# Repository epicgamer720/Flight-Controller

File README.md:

# Rocket Flight Controller

A custom, open-source flight computer for model and high-power rockets, built around an STM32F722 with onboard IMU, barometer, GPS, pyro deployment, quad servo outputs, and microSD logging. Designed from scratch in KiCad.

## Why I built it

Wanted to get my feet wet with more mixed PCB design. I designed this as a base for firmware and testing I plan to designing another one after I build and test this one on actual rockets. I plan to use this for my rocketry team for active control and data logging 

## Use cases

- **Dual-deploy recovery**: pyro drogue at apogee, then a servo mechanically releases the main at a set altitude. (This rev routes one pyro channel; the servo is the second deploy.)
- **Active stabilization**: drive the four servo outputs for thrust-vector control or canard/fin steering during boost.
- **Flight data logging**: log IMU, barometer, and GPS to microSD for post-flight analysis (apogee, max velocity, flight path).
- **GPS tracking**: downrange tracking and finding the rocket after landing.
- **Telemetry**: LoRa (SX1262, 915 MHz) for live altitude/position downlink.
- **General avionics dev board**: the IMU + baro + GPS + servo + logging combo also works for drones, RC, robotics, or balloon payloads.

## Specifications

| Subsystem | Part / detail |
|---|---|
| MCU | STM32F722RET6, Cortex-M7, up to 216 MHz |
| IMU | ISM330DHCX, 6-axis accel (±16 g) + gyro, SPI (built rev; early docs said ICM-45686) |
| Barometer | BMP580, altitude / apogee detection (I²C) |
| Storage | microSD (SDMMC1, 4-bit), 200 Hz binary flight log |
| Recovery | 1 pyro channel (gate PB13, continuity sense PC1) + servo main-release, giving dual-deploy without a 2nd pyro (2 designed) |
| Control | 4× servo outputs (TIM2) for TVC / fin / canard; one doubles as the main-release |
| GPS | NMEA module on USART6, JST-GH + PRTR5V0U2X ESD protection |
| Telemetry | LoRa Wio-SX1262 (915 MHz, TCXO): live downlink + over-air TX-power control, verified on hardware |
| Power | 2S LiPo, BQ25883 charger, USB-C |
| Status | WS2812 RGB status LED |

## Bench status (July 2026)

All subsystems green on hardware: IMU, barometer, SD logging, LoRa radio
(TCXO confirmed, telemetry transmitting), charger, GPS UART. The firmware
builds with `arm-none-eabi-gcc` (GitHub CI), has been flashed to the board,
and passes its on-console **preflight** GO/NO-GO check, so it is **bench-verified,
not flight-tested**. The deploy-critical logic is exercised host-side by a SIL
harness (a faithful Python transcription of the state machine / Kalman / pyro
paths) plus 245 stdlib-`unittest` tests, and went through several adversarial
multi-agent review passes.

Flight hardening on top of the earlier IWDG watchdog + reset-cause logging,
Kalman altitude filter with outlier gating, and pad-drift baro tracking:

- **Hardened arm gate**: refuses to arm without pyro continuity, adequate
  battery, near-zero velocity, *and* a plausible skyward orientation
  (`ARM_UP_AXIS`).
- **Fault-independent backup deploy**: a backup timer fires the charge even
  through `ST_FAULT` with dead sensors, so a sensor loss isn't a lawn-dart.
- **Servo dual-deploy**: a main-release servo held SAFE through ascent,
  actuated at the main-deploy altitude (no 2nd pyro needed).
- **Flash config v2**: runtime-tunable apogee/backup timer + last-GPS-for-
  recovery, migrating cleanly from v1.
- **Telemetry v3**: sequence / packet-delivery ratio, last-event echo,
  main-alt read-back, STM32 die-temp, and over-air TX-power control.
- Gyro-cal stationarity check, IMU-freeze detection, self-healing ground
  FAULT, failed-deploy detection, deeper anti-replay nonce window, baro
  temperature compensation, a recovery LED strobe (WS2812), and a STOP-mode
  low-power `sleep`.

**Tune before flight**: the defaults are placeholders, not final: `ARM_UP_AXIS`
(confirm the skyward IMU axis), the apogee/backup timer per motor (`apogee`
console cmd), the servo endpoints, and the flight thresholds (`LAUNCH_G`,
`MAIN_ALT`, debounces). The baro-only Kalman also lags true apogee by ~70 m in
SIL at `KAL_Q_ACCEL=4`, a candidate to raise once real flight data exists.
Also remaining: ground-station pin map + build, and a healthier USB cable.

## BOM

| Name | Purpose | Qty | Unit Cost (USD) | Line Cost (USD) | Link | Distributor | Notes |
|---|---|---|---|---|---|---|---|
| 1uF | Decoupling cap (0603, X7R, 25V) | 4 | $0.02 | $0.08 | Link | Digikey | |
| 10uF | Bulk decoupling (0805, X5R, 16V) | 7 | $0.10 | $0.40 | Link | Digikey | |
| 47nF | Filter cap, possibly BQ25883 ILIM or feedback (0603) | 1 | $0.02 | $0.02 | Link | Digikey | |
| 44uF | Unusual value, check schematic | 1 | $0.50 | $0.50 | Link | Digikey |  |
| 10uF | Bulk decoupling (0805, X5R) | 2 | $0.10 | $0.20 | Link | Digikey | |
| 22uF | Switching regulator output cap (0805, X5R, 16V) | 3 | $0.20 | $0.60 | Link | Digikey | |
| 100nF | Generic decoupling, 0402 or 0603 X7R | 12 | $0.01 | $0.12 | Link | Digikey | |
| 2.2uF | STM32 VCAP_1 (PA0) capacitor, 2.2µF X7R 0603 | 1 | $0.05 | $0.05 | Link | Digikey | Critical for MCU core regulator stability |
| 22uF | Regulator input/output cap | 2 | $0.20 | $0.40 | Link | Digikey | |
| 2.2uF | Second VCAP or filter | 1 | $0.05 | $0.05 | Link | Digikey | |
| 20pF | HSE crystal load capacitor (matches X322525MOB4SI) | 2 | $0.05 | $0.10 | Link | Digikey | Value depends on crystal CL spec, verify |
| 6.8pF | LSE 32.768kHz crystal load capacitor | 2 | $0.05 | $0.10 | Link | Digikey | Adjust to match crystal CL = ~7pF |
| 100nF | Generic decoupling, 0402 or 0603 | 5 | $0.01 | $0.05 | Link | Digikey | |
| TF-01A | MicroSD card socket (push-pull or hinged) | 1 | $1.50 | $1.50 | Link | LCSC | LCSC-style part; Hirose DM3AT-SF-PEJM5 is a Digikey alternative |
| LED | Generic indicator LED 0603 (e.g., power indicator) | 1 | $0.10 | $0.10 | Link | Digikey | |
| WS2812B-2020 | Addressable RGB status LED, single-wire (KMK-style) | 1 | $0.30 | $0.30 | Link | LCSC | Cheaper on LCSC than Digikey |
| PRTR5V0U2X | Dual-line TVS ESD protection for GPS UART | 1 | $0.35 | $0.35 | Link | Digikey | Nexperia, SOT-143B |
| Screw_Terminal_01x02 | 2-pin screw terminal for pyro outputs and battery | 3 | $1.20 | $3.60 | Link | Digikey | |
| BM05B-GHS-TBT_LF__SN__N_ | JST-GH 5-pin top-entry connector (GPS, Pixhawk standard) | 1 | $0.55 | $0.55 | Link | Digikey | JST part #BM05B-GHS-TBT(LF)(SN)(N) |
| FCM1608KF-601T03 | Ferrite bead 600Ω @ 100MHz, 0603, analog supply filter | 1 | $0.10 | $0.10 | Link | Digikey | Taiyo Yuden |
| DFE252012F-1R0M=P2 | Power inductor 1.0µH, 2520 case, buck output (LMR51430?) | 1 | $0.40 | $0.40 | Link | Digikey | Toko/Murata, ~3.6A saturation |
| XFL4020-152MEC | Power inductor 1.5µH, 4×4mm, switcher output | 1 | $1.50 | $1.50 | Link | Digikey | Coilcraft, very low DCR |
| YHNR3015-5R6M | Power inductor 5.6µH, likely buck-boost (TPS63070) | 1 | $0.30 | $0.30 | Link | LCSC | Sunlord, LCSC-stocked |
| AO3400A | N-channel logic-level MOSFET, SOT-23, pyro low-side switch | 2 | $0.15 | $0.30 | Link | Digikey | |
| 5.1K Ohm | Pullup/divider for USB-C CC1/CC2 (5.1k for device-mode detect) | 2 | $0.01 | $0.02 | Link | Digikey | Required for USB-C device mode |
| .383k Ohm | Precision resistor, likely BQ25883 ISET or regulator FB | 1 | $0.10 | $0.10 | Link | Digikey | |
| 5.23K Ohm | Feedback divider for switching regulator | 1 | $0.05 | $0.05 | Link | Digikey | 1% precision |
| 30.1K Ohm | Feedback divider (top resistor) for switching regulator | 1 | $0.05 | $0.05 | Link | Digikey | 1% precision |
| 10K Ohm | Generic pullups/pulldowns, gate pulldowns on MOSFETs (0603) | 19 | $0.01 | $0.19 | Link | Digikey | Cheap in bulk |
| 100K Ohm | Continuity divider top (pyro sense) | 1 | $0.01 | $0.01 | Link | Digikey | |
| 22.1K Ohm | Precision feedback or current-set resistor | 1 | $0.05 | $0.05 | Link | Digikey | 1% precision |
| 100K Ohm | More continuity dividers | 2 | $0.01 | $0.02 | Link | Digikey | |
| 100 Ohm | Gate series resistors on pyro MOSFETs | 3 | $0.01 | $0.03 | Link | Digikey | |
| Conn_01x03 | 3-pin header, likely servo/PWM outputs or programming | 4 | $0.30 | $1.20 | Link | Digikey | (2.54mm standard) |
| TS-1088-AR02016 | Tactile switch for boot/reset buttons | 2 | $0.20 | $0.40 | Link | Digikey | Cheap SMD tactile, also on LCSC |
| STM32F722RETx | Main MCU, ARM Cortex-M7, 216MHz, 512KB flash | 1 | $10.50 | $10.50 | Link | Digikey/Mouser | Check stock: F7 series can be supply-constrained |
| BQ25883RGER | Single-cell Li-ion charger w/ I2C, up to 2A | 1 | $3.80 | $3.80 | Link | Digikey | TI, QFN-24 |
| ICM-45686 | 6-axis IMU (accel + gyro), low-noise, SPI | 1 | $12.00 | $12.00 | Link | Digikey | TDK InvenSense, LGA-14. Newer than ICM-42688-P |
| BMP580 | Barometric pressure / altitude sensor (high resolution) | 1 | $4.20 | $4.20 | Link | Digikey | Bosch Sensortec, replaces BMP388 |
| TPS63070RNMR | Buck-boost regulator, 2A, 2-16V in | 1 | $3.60 | $3.60 | Link | Digikey | TI, VQFN-15 |
| LMR51430 | Buck regulator, 3A, simple step-down | 1 | $1.40 | $1.40 | Link | Digikey | TI, SOT-23-6 family |
| TYPE-C 16PIN 2MD(073) | USB-C connector, 16-pin (USB 2.0 only) | 1 | $0.50 | $0.50 | Link | LCSC | LCSC-style part number. Alt: GCT USB4105-GF-A (Digikey) |
| X322525MOB4SI | HSE crystal 25MHz, SMD 3225 | 1 | $0.60 | $0.60 | Link | LCSC | Yangxing. Alt: Abracon ABM8G-25.000MHZ |
| Q13FC1350000400 | LSE crystal 32.768kHz (RTC) | 1 | $0.40 | $0.40 | Link | Digikey | Epson FC-135 |

## Firmware & software

The flight firmware and ground tools live in this repo:

| Where | What |
|---|---|
| [`flight-controller/`](flight-controller/) | STM32F722 flight firmware: sensors, Kalman altitude filter, flight state machine, hardened arm gate + interlocked pyro control, fault-independent backup deploy, servo main-release, flash config v2, SD logging, LoRa telemetry v3 (die-temp + TX-power control), IWDG watchdog, USB console (`preflight`, `apogee`, `sleep`, …) |
| [`ground-station/`](ground-station/) | RP2040 + SX1262 LoRa ground station (RadioLib sketch; pin map pending) |
| [`shared/`](shared/) | `protocol.h`, the single source of truth for the radio link + packet formats |
| [`tools/`](tools/) | **Flight Deck** ops dashboard (recovery bearing/distance, baro-vs-GPS apogee check, telemetry-loss alarm, satellite GPS ground-track, SD `.bin` replay), one-page flight report, DFU flash helper (`flash.py`), serial monitor, log/telemetry decoders (`decode_log.py --summary`) |
| [`tests/`](tests/) | 245 host-side unit tests + a SIL flight harness (`py -m unittest discover -s tests`) |
| [`docs/FIRMWARE.md`](docs/FIRMWARE.md) | build / flash / console / bench guide |
| [`docs/PINMAP.md`](docs/PINMAP.md) | authoritative pin map extracted from the KiCad netlist |

## This project uses:

- [KiCad](https://www.kicad.org/)
- [STM32CubeMX](https://www.st.com/en/development-tools/stm32cubemx.html)
- [easyeda2kicad.py](https://github.com/uPesy/easyeda2kicad.py)
- [Hack Club Blueprint](https://blueprint.hackclub.com/)

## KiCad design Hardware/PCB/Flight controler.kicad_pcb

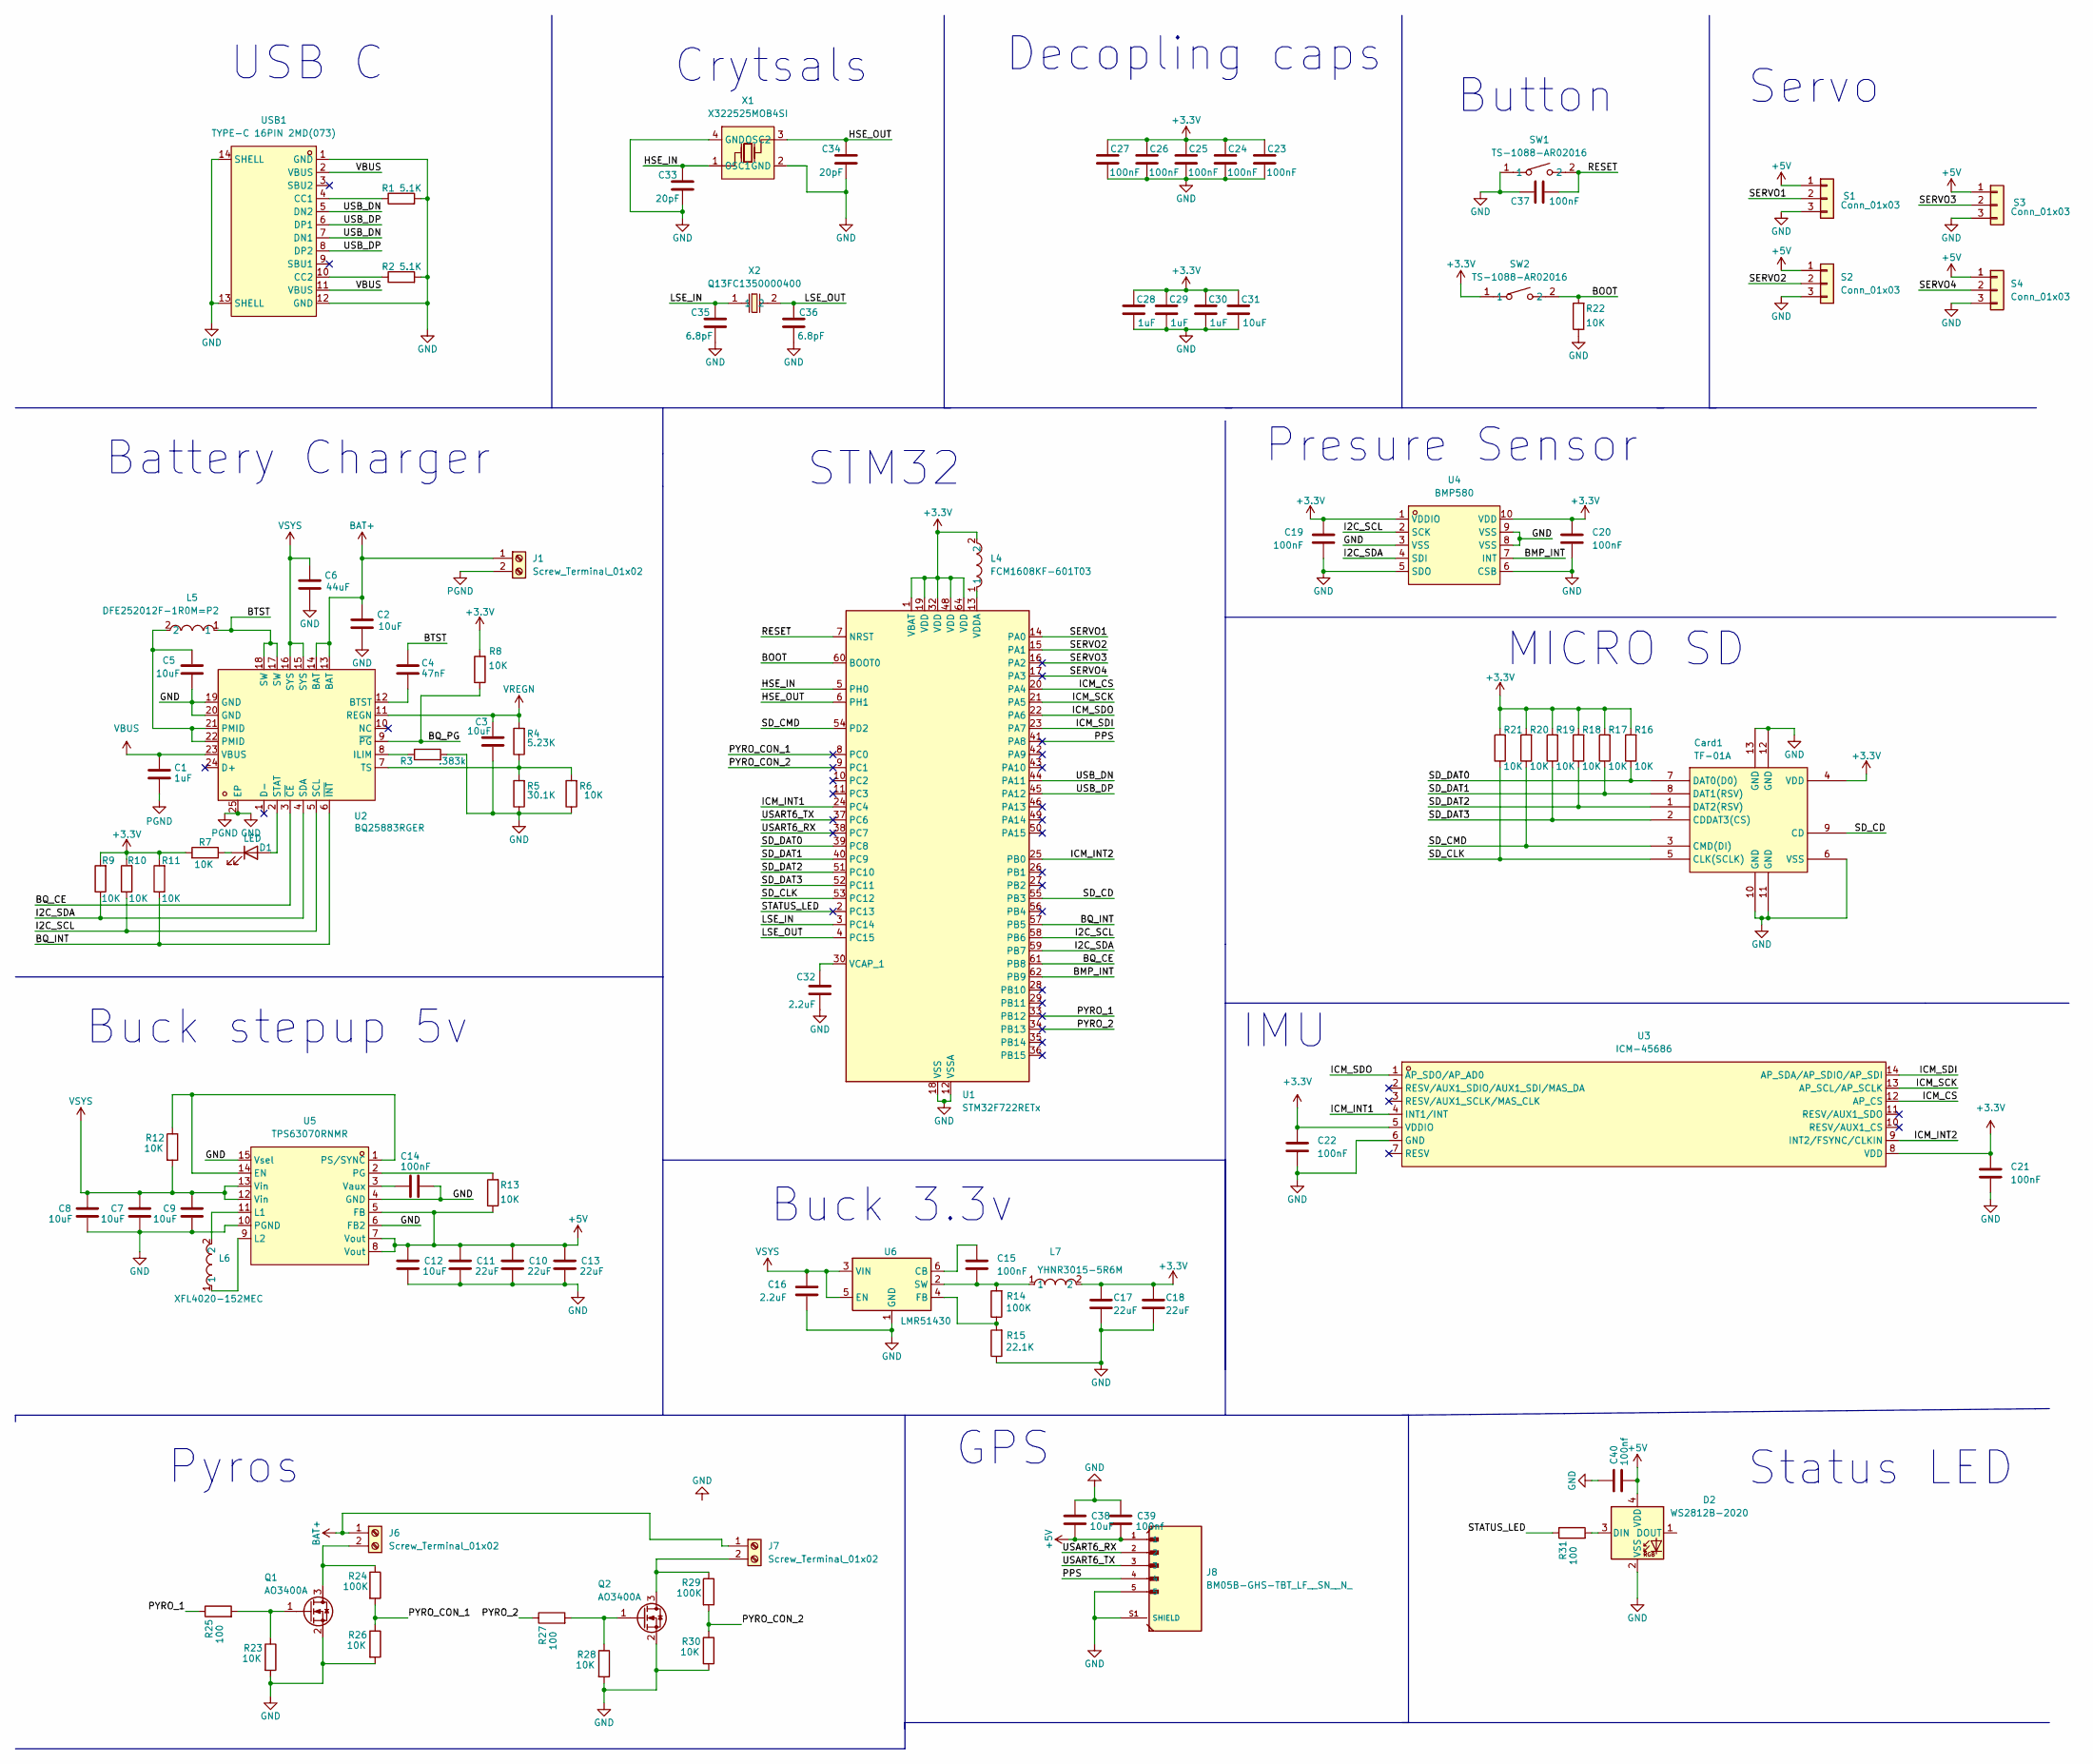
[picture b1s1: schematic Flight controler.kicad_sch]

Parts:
C1, C28, C29, C30: 1uF; C_0402_1005Metric
C2, C9, C12, C38: 10uF; C_0603_1608Metric
C3, C5, C31: 10uF; C_0402_1005Metric
C4: 47nF; C_0201_0603Metric
C6: 44uF; C_0603_1608Metric
C7, C8: 10uF; C_0805_2012Metric
C10, C11, C13: 22uF; C_0805_2012Metric
C14, C15, C19, C20, C21, C22, C23, C24, C25, C26, C27, C37: 100nF; C_0201_0603Metric
C16: 2.2uF; C_0603_1608Metric
C17, C18: 22uF; C_0402_1005Metric
C32: 2.2uF; C_0201_0603Metric
C33, C34: 20pF; C_0201_0603Metric
C35, C36: 6.8pF; C_0201_0603Metric
C39, C40: 100nf; C_0603_1608Metric
Card1: TF-01A; TF-SMD_TF-01A; LCSC Part C91145
D1: LED; LED_0402_1005Metric
D2: WS2812B-2020; LED_WS2812B-2020_PLCC4_2.0x2.0mm
J1, J6, J7: Screw_Terminal_01x02; TerminalBlock_Xinya_XY308-2.54-2P_1x02_P2.54mm_Horizontal
J8: BM05B-GHS-TBT_LF__SN__N_; JST_BM05B-GHS-TBT_LF__SN__N_
L4: FCM1608KF-601T03; L0603; LCSC Part C141723
L5: DFE252012F-1R0M=P2; L2520; LCSC Part C435392
L6: XFL4020-152MEC; IND-SMD_L4.0-W4.0-A; LCSC Part C3033018
L7: YHNR3015-5R6M; IND-SMD_L3.0-W3.0; LCSC Part C18236327
Q1, Q2: AO3400A; SOT-23
R1, R2: 5.1K; R_0201_0603Metric
R3: .383k; R_0201_0603Metric
R4: 5.23K; R_0201_0603Metric
R5: 30.1K; R_0201_0603Metric
R6, R7, R8, R9, R10, R11, R12, R13, R16, R17, R18, R19, R20, R21, R22, R23, R26, R28, R30: 10K; R_0201_0603Metric
R14: 100K; R_0402_1005Metric
R15: 22.1K; R_0402_1005Metric
R24, R29: 100K; R_0201_0603Metric
R25, R27, R31: 100; R_0201_0603Metric
S1, S2, S3, S4: Conn_01x03; PinHeader_1x03_P2.54mm_Vertical
SW1, SW2: TS-1088-AR02016; SW-SMD_L3.9-W3.0-P4.45; LCSC Part C720477
U1: STM32F722RETx; LQFP-64_10x10mm_P0.5mm
U2: BQ25883RGER; VFQFPN-24_L4.0-W4.0-P0.50-BL-EP2.8; LCSC Part C544362
U3: ICM-45686; LGA-14_L3.0-W2.5-P0.50-TL; LCSC Part C22459454
U4: BMP580; LGA-10_L2.0-W2.0-P0.50-TL_BMP580; LCSC Part C22391138
U5: TPS63070RNMR; VQFN-HR-15_L3.0-W2.5-P0.50-BL_TPS63070RNMR; LCSC Part C109322
U6: LMR51430; SOT-23-6
USB1: TYPE-C 16PIN 2MD(073); USB-C-SMD_TYPE-C-6PIN-2MD-073; LCSC Part C2765186
X1: X322525MOB4SI; CRYSTAL-SMD_4P-L3.2-W2.5-BL; LCSC Part C9006
X2: Q13FC1350000400; FC-135R_L3.2-W1.5; LCSC Part C32346

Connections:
+3.3V: C17.1, C18.1, C19.1, C20.1, C21.1, C22.1, C23.1, C24.1, C25.1, C26.1, C27.1, C28.1, C29.1, C30.1, C31.1, Card1.4 (VDD), L4.2, L7.2, R7.2, R8.2, R9.2, R10.2, R11.2, R16.2, R17.2, R18.2, R19.2, R20.2, R21.2, SW2.1, U1.1 (VBAT), U1.19 (VDD), U1.32 (VDD), U1.48 (VDD), U1.64 (VDD), U3.5 (VDDIO), U3.8 (VDD), U4.1 (VDDIO), U4.10 (VDD); also elsewhere on the board
+5V: C10.1, C11.1, C12.1, C13.1, C38.2, C39.2, C40.2, D2.4 (VDD), J8.1, R13.1, S1.1, S2.1, S3.1, S4.1, U5.5 (FB), U5.7 (Vout), U5.8 (Vout); also elsewhere on the board
/BMP_INT: U1.62 (PB9), U4.7 (INT)
/BOOT: R22.2, SW2.2, U1.60 (BOOT0); also elsewhere on the board
/BQ_CE: U1.61 (PB8), U2.3 (~CE)
/BQ_INT: R11.1, U1.57 (PB5), U2.6 (~INT)
/BQ_PG: R8.1, U2.9 (~PG)
/BTST: C4.1, L5.1, U2.17 (SW), U2.18 (SW)
/HSE_IN: C33.1, U1.5 (PH0), X1.1 (OSC1)
/HSE_OUT: C34.1, U1.6 (PH1), X1.3 (OSC2)
/I2C_SCL: R10.1, U1.58 (PB6), U2.5 (SCL), U4.2 (SCK)
/I2C_SDA: R9.1, U1.59 (PB7), U2.4 (SDA), U4.4 (SDI)
/ICM_CS: U1.20 (PA4), U3.12 (AP_CS)
/ICM_INT1: U1.24 (PC4), U3.4 (INT1/INT)
/ICM_INT2: U1.25 (PB0), U3.9 (INT2/FSYNC/CLKIN)
/ICM_SCK: U1.21 (PA5), U3.13 (AP_SCL/AP_SCLK)
/ICM_SDI: U1.23 (PA7), U3.14 (AP_SDA/AP_SDIO/AP_SDI)
/ICM_SDO: U1.22 (PA6), U3.1 (AP_SDO/AP_AD0)
/LSE_IN: C35.1, U1.3 (PC14), X2.1
/LSE_OUT: C36.1, U1.4 (PC15), X2.2
/PPS: J8.4, U1.41 (PA8)
/PYRO_1: R25.1, U1.33 (PB12)
/PYRO_2: R27.1, U1.34 (PB13)
/PYRO_CON_1: R24.2, R26.1, U1.8 (PC0)
/PYRO_CON_2: R29.2, R30.1, U1.9 (PC1)
/RESET: C37.2, SW1.2, U1.7 (NRST); also elsewhere on the board
/SD_CD: Card1.9 (CD), U1.55 (PB3)
/SD_CLK: Card1.5 (CLK(SCLK)), R21.1, U1.53 (PC12)
/SD_CMD: Card1.3 (CMD(DI)), R20.1, U1.54 (PD2)
/SD_DAT0: Card1.7 (DAT0(D0)), R16.1, U1.39 (PC8)
/SD_DAT1: Card1.8 (DAT1(RSV)), R17.1, U1.40 (PC9)
/SD_DAT2: Card1.1 (DAT2(RSV)), R18.1, U1.51 (PC10)
/SD_DAT3: Card1.2 (CDDAT3(CS)), R19.1, U1.52 (PC11)
/SERVO1: S1.2, U1.14 (PA0); also elsewhere on the board
/SERVO2: S2.2, U1.15 (PA1); also elsewhere on the board
/SERVO3: S3.2, U1.16 (PA2); also elsewhere on the board
/SERVO4: S4.2, U1.17 (PA3); also elsewhere on the board
/STATUS_LED: R31.1, U1.2 (PC13)
/USART6_RX: J8.2, U1.38 (PC7); also elsewhere on the board
/USART6_TX: J8.3, U1.37 (PC6); also elsewhere on the board
/USB_DN: U1.44 (PA11), USB1.5 (DN2), USB1.7 (DN1)
/USB_DP: U1.45 (PA12), USB1.6 (DP1), USB1.8 (DP2)
BAT+: C2.1, J1.1, J6.1, J7.1, U2.13 (BAT), U2.14 (BAT); also elsewhere on the board
GND: C1.2, C2.2, C3.2, C5.2, C6.2, C7.2, C8.2, C9.2, C10.2, C11.2, C12.2, C13.2, C14.2, C16.2, C17.2, C18.2, C19.2, C20.2, C21.2, C22.2, C23.2, C24.2, C25.2, C26.2, C27.2, C28.2, C29.2, C30.2, C31.2, C32.2, C33.2, C34.2, C35.2, C36.2, C37.1, C38.1, C39.1, C40.1, Card1.6 (VSS), Card1.10 (GND), Card1.11 (GND), Card1.12 (GND), Card1.13 (GND), D2.2 (VSS), J1.2, J8.5, J8.S1 (SHIELD), J8.S2 (SHIELD), Q1.2 (S), Q2.2 (S), R1.2, R2.2, R3.2, R5.1, R6.1, R15.1, R22.1, R23.2, R26.2, R28.2, R30.2, S1.3, S2.3, S3.3, S4.3, SW1.1, U1.12 (VSSA), U1.18 (VSS), U1.31 (VSS), U1.47 (VSS), U1.63 (VSS), U2.19 (GND), U2.20 (GND), U2.25 (EP), U3.6 (GND), U4.3 (VSS), U4.5 (SDO), U4.6 (CSB), U4.8 (VSS), U4.9 (VSS), U5.4 (GND), U5.6 (FB2), U5.10 (PGND), U5.15 (Vsel), U6.1 (GND), USB1.1 (GND), USB1.12 (GND), USB1.13 (SHELL), USB1.14 (SHELL), X1.2 (GND), X1.4 (GND); also elsewhere on the board
unnamed: C5.1, L5.2, U2.21 (PMID), U2.22 (PMID)
unnamed: D1.2 (A), U2.2 (STAT)
unnamed: D1.1 (K), R7.1
unnamed: D2.3 (DIN), R31.2
unnamed: J6.2, Q1.3 (D), R24.1
unnamed: J7.2, Q2.3 (D), R29.1
unnamed: Q1.1 (G), R23.1, R25.2
unnamed: Q2.1 (G), R27.2, R28.1
unnamed: C32.1, U1.30 (VCAP_1)
unnamed: L4.1, U1.13 (VDDA)
unnamed: C4.2, U2.12 (BTST)
unnamed: R3.1, U2.8 (ILIM)
unnamed: R4.1, R5.2, R6.2, U2.7 (TS)
unnamed: R12.1, U5.1 (PS/SYNC), U5.14 (EN)
unnamed: L6.2, U5.11 (L1)
unnamed: L6.1, U5.9 (L2)
unnamed: R13.2, U5.2 (PG)
unnamed: C14.1, U5.3 (Vaux)
unnamed: C15.1, U6.6 (CB)
unnamed: R14.1, R15.2, U6.4 (FB)
unnamed: C15.2, L7.1, R14.2, U6.2 (SW)
unnamed: R1.1, USB1.4 (CC1)
unnamed: R2.1, USB1.10 (CC2)
VBUS: C1.1, U2.23 (VBUS), USB1.2 (VBUS), USB1.11 (VBUS)
VREGN: C3.1, R4.2, U2.11 (REGN)
VSYS: C6.1, C7.1, C8.1, C9.1, C16.1, R12.2, U2.15 (SYS), U2.16 (SYS), U5.12 (Vin), U5.13 (Vin), U6.3 (VIN), U6.5 (EN)

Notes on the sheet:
STM32
Button
Buck stepup 5v
Crytsals
Presure Sensor
GPS
USB C
MICRO SD
IMU
Battery Charger
Buck 3.3v
Pyros
Status LED
Servo
Decopling caps

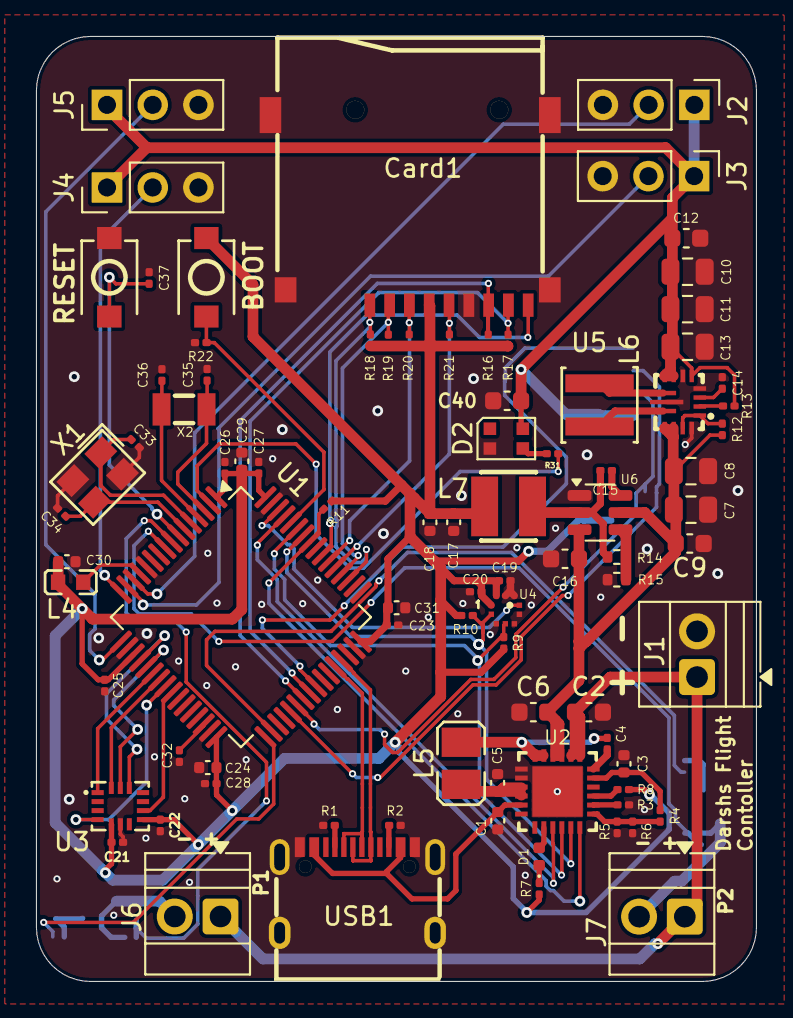
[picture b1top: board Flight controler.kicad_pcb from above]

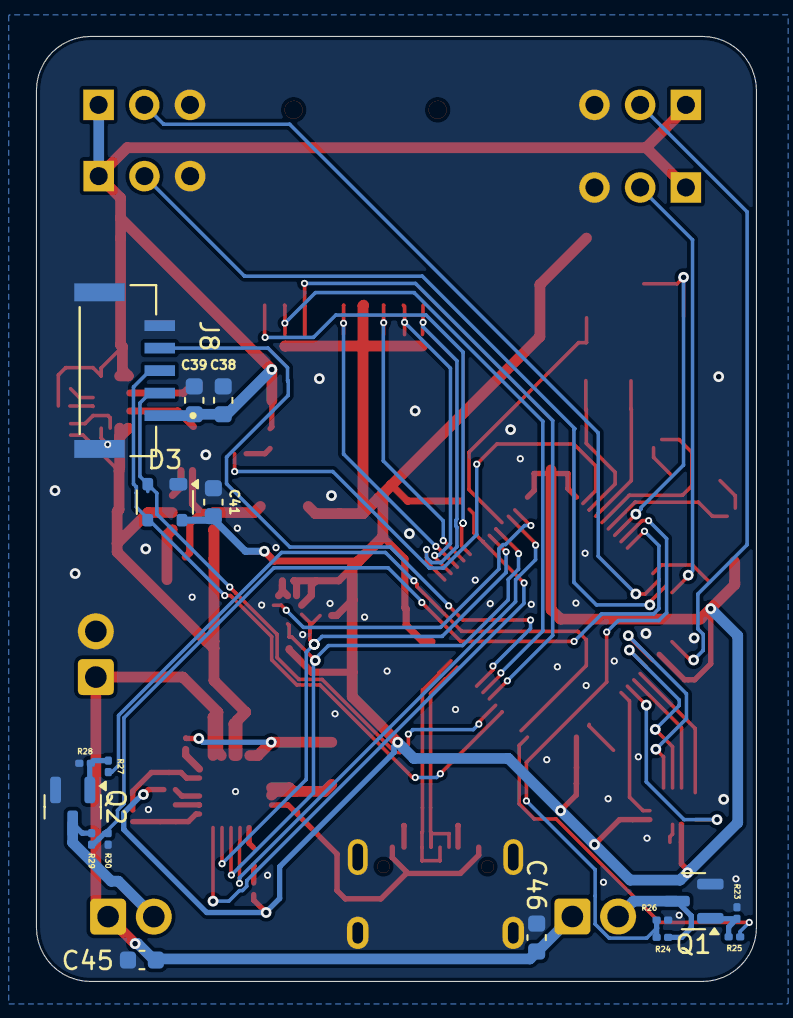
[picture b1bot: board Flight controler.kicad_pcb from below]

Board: 2 copper layers, 40.0 x 52.5 mm, 103 parts (17 on the bottom side), 70 nets.

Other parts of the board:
BOOT: TS-1088-AR02016; SW-SMD_L3.9-W3.0-P4.45
C41, C45, C46: 100nf; C_0603_1608Metric
D3: PRTR5V0U2X; SOT-143
J2, J3, J4, J5: Conn_01x03; PinHeader_1x03_P2.54mm_Vertical
RESET: TS-1088-AR02016; SW-SMD_L3.9-W3.0-P4.45

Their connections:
+3.3V: BOOT.1, C41.1, D3.4 (VCC); also elsewhere on the board
+5V: J2.1, J3.1, J4.1, J5.1; also elsewhere on the board
/BOOT: BOOT.2; also elsewhere on the board
/RESET: RESET.2; also elsewhere on the board
/SERVO1: J2.2; also elsewhere on the board
/SERVO2: J3.2; also elsewhere on the board
/SERVO3: J4.2; also elsewhere on the board
/SERVO4: J5.2; also elsewhere on the board
/USART6_RX: D3.2 (I/O1); also elsewhere on the board
/USART6_TX: D3.3 (I/O2); also elsewhere on the board
BAT+: C45.2, C46.2; also elsewhere on the board
GND: C41.2, C45.1, C46.1, D3.1 (GND), J2.3, J3.3, J4.3, J5.3, RESET.1; also elsewhere on the board

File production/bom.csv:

Designator,Footprint,Quantity,Value,LCSC Part #
"BOOT, RESET",SW-SMD_L3.9-W3.0-P4.45,2,TS-1088-AR02016,C720477
"C1, C28, C29, C30",0402,4,1uF,
"C10, C11, C13",0805,3,22uF,
"C12, C2, C9",0603,3,10uF,
"C14, C15, C19, C20, C21, C22, C23, C24, C25, C26, C27, C37",0201,12,100nF,
C16,0603,1,2.2uF,
"C17, C18",0402,2,22uF,
"C3, C31, C5",0402,3,10uF,
C32,0201,1,2.2uF,
"C33, C34",0201,2,20pF,
"C35, C36",0201,2,6.8pF,
C4,0201,1,47nF,
C6,0603,1,44uF,
"C7, C8",0805,2,10uF,
CARD1,TF-SMD_TF-01A,1,TF-01A,C91145
D1,0402,1,LED,
J1,TerminalBlock_Xinya_XY308-2.54-2P_1x02_P2.54mm_Horizontal,1,Screw_Terminal_01x02,
"J2, J3",PinHeader_1x03_P2.54mm_Vertical,2,Conn_01x03,
L4,L0603,1,FCM1608KF-601T03,C141723
L5,L2520,1,DFE252012F-1R0M=P2,C435392
L6,IND-SMD_L4.0-W4.0-A,1,XFL4020-152MEC,C3033018
L7,IND-SMD_L3.0-W3.0,1,YHNR3015-5R6M,C18236327
"R1, R2",0201,2,5.1K,
"R10, R11, R12, R13, R16, R17, R18, R19, R20, R21, R22, R6, R7, R8, R9",0201,15,10K,
R14,0402,1,100K,
R15,0402,1,22.1K,
R3,0201,1,383,
R4,0201,1,5.23K,
R5,0201,1,30.1K,
U1,LQFP-64_10x10mm_P0.5mm,1,STM32F722RETx,
U2,VFQFPN-24_L4.0-W4.0-P0.50-BL-EP2.8,1,BQ25883RGER,C544362
U3,LGA-14_L3.0-W2.5-P0.50-TL,1,ICM-45686,C22459454
U4,LGA-10_L2.0-W2.0-P0.50-TL_BMP580,1,BMP580,C22391138
U5,VQFN-HR-15_L3.0-W2.5-P0.50-BL_TPS63070RNMR,1,TPS63070RNMR,C109322
U6,SOT-23-6,1,LMR51430,
USB1,USB-C-SMD_TYPE-C-6PIN-2MD-073,1,TYPE-C 16PIN 2MD(073),C2765186
X1,CRYSTAL-SMD_4P-L3.2-W2.5-BL,1,X322525MOB4SI,C9006
X2,FC-135R_L3.2-W1.5,1,Q13FC1350000400,C32346

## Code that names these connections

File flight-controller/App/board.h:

#pragma once
/* ============================================================
 * board.h: authoritative hardware map for the Flight Controller
 * Extracted from KiCad netlist (Downloads/fe/Flight controler.kicad_sch,
 * exported 2026-07-07 via kicad-cli). DO NOT invent pins; if it is not
 * here, it is not connected on the board.
 *
 * MCU: STM32F722RET6, LQFP64. HSE 25 MHz (X322525MOB4SI), LSE 32.768 kHz.
 * No SWD (PA13/PA14 unconnected); debug via USB-CDC, flash via DFU.
 * ============================================================ */
#include "stm32f7xx_hal.h"

/* ---- IMU: ISM330DHCX (U7) on shared SPI1, mode 0, <=10 MHz ---- */
#define IMU_CS_PORT        GPIOA
#define IMU_CS_PIN         GPIO_PIN_4    /* /ISM_CS, 10K pull-up R23 */
#define IMU_INT1_PORT      GPIOC
#define IMU_INT1_PIN       GPIO_PIN_4    /* /ISM_INT1 */
#define IMU_INT2_PORT      GPIOB
#define IMU_INT2_PIN       GPIO_PIN_0    /* /ISM_INT2 */

/* ---- LoRa: Wio-SX1262 module (U3) on shared SPI1, mode 0 (mandatory) ---- */
#define LORA_CS_PORT       GPIOA
#define LORA_CS_PIN        GPIO_PIN_9    /* /LORA_CS, 10K pull-up R24 */
#define LORA_IRQ_PORT      GPIOA
#define LORA_IRQ_PIN       GPIO_PIN_10   /* /LORA_IRQ = DIO1, EXTI15_10 */
#define LORA_BUSY_PORT     GPIOB
#define LORA_BUSY_PIN      GPIO_PIN_1    /* /LORA_BUSY */
#define LORA_RST_PORT      GPIOA
#define LORA_RST_PIN       GPIO_PIN_15   /* /LORA_RST, active low */
/* /LORA_RF_SW1 = PB2: driven internally by the module via DIO2.
 * MUST stay high-impedance (analog mode). NEVER configure as output. */
#define LORA_RFSW_PORT     GPIOB
#define LORA_RFSW_PIN      GPIO_PIN_2

/* ---- SPI1 (shared IMU + LoRa): SCK=PA5 MISO=PA6 MOSI=PA7, AF5 ----
 * APB2 = 108 MHz; prescaler /16 => 6.75 MHz (within both parts' limits). */

/* ---- Barometer: BMP580 (U4) on I2C1 (PB6=SCL PB7=SDA, 4.7K pull-ups) ---- */
#define BMP_INT_PORT       GPIOB
#define BMP_INT_PIN        GPIO_PIN_9    /* /BMP_INT */
/* I2C addresses to probe: 0x46 then 0x47 (7-bit) */

/* ---- Charger: BQ25883 (U2) on I2C1, 7-bit addr 0x6B ---- */
#define BQ_INT_PORT        GPIOB
#define BQ_INT_PIN         GPIO_PIN_5    /* /BQ_INT, 10K pull-up, open-drain */
#define BQ_CE_PORT         GPIOB
#define BQ_CE_PIN          GPIO_PIN_8    /* /BQ_CE: ~CE, LOW = charge enabled */

/* ---- GPS: external module on JST-GH J8, USART6 AF8 ---- */
#define GPS_TX_PORT        GPIOC
#define GPS_TX_PIN         GPIO_PIN_6    /* /USART6_TX (FC->GPS) */
#define GPS_RX_PORT        GPIOC
#define GPS_RX_PIN         GPIO_PIN_7    /* /USART6_RX (GPS->FC) */
#define GPS_PPS_PORT       GPIOA
#define GPS_PPS_PIN        GPIO_PIN_8    /* /PPS (input) */

/* ---- Pyro: ONE channel. Low-side AO3400A (Q2), terminal J7 off BAT+ ----
 * Gate: 100R series (R27) + 10K pulldown (R28). Fire = drive HIGH.
 * Continuity: J7.2 -100K(R29)-> PC1 -10K(R30)-> GND divider (ratio 1/11).
 * With e-match fitted and gate OFF, PC1 ~= VBAT/11 (e.g. 8.2V -> ~0.75V).
 * NOTE: schematic label PYRO_CON_1 on PC0 is dangling (unrouted), unused. */
#define PYRO1_GATE_PORT    GPIOB
#define PYRO1_GATE_PIN     GPIO_PIN_13   /* /PYRO_2 net: boot-safe LOW, push-pull */
#define PYRO1_SENSE_PORT   GPIOC
#define PYRO1_SENSE_PIN    GPIO_PIN_1    /* /PYRO_CON_2 = ADC123_IN11 */
#define PYRO1_SENSE_ADC_CH ADC_CHANNEL_11
#define PYRO_SENSE_DIV     11.0f         /* (100K+10K)/10K */

/* ---- Servos: 4x on TIM2 CH1..CH4 (AF1), 50 Hz ---- */
#define SERVO1_PORT        GPIOA
#define SERVO1_PIN         GPIO_PIN_0    /* TIM2_CH1 */
#define SERVO2_PORT        GPIOA
#define SERVO2_PIN         GPIO_PIN_1    /* TIM2_CH2 */
#define SERVO3_PORT        GPIOA
#define SERVO3_PIN         GPIO_PIN_2    /* TIM2_CH3 */
#define SERVO4_PORT        GPIOA
#define SERVO4_PIN         GPIO_PIN_3    /* TIM2_CH4 */
#define NUM_SERVO          4

/* ---- SD card: SDMMC1 4-bit (all lines 10K pulled up) ---- */
/* D0=PC8 D1=PC9 D2=PC10 D3=PC11 CLK=PC12 CMD=PD2, AF12 */
#define SD_CD_PORT         GPIOB
#define SD_CD_PIN          GPIO_PIN_3    /* card detect, closed-to-GND when inserted: use internal pull-up, LOW = card present */

/* ---- USB: OTG_FS device, USB-C with 5.1K CC pulldowns (UFP) ---- */
/* DM=PA11 DP=PA12, AF10 */

/* ---- Status LED: single WS2812B-2020 data-in from PC13 via 100R ----
 * PC13 is a low-drive (~2 MHz) pin: bit-banged with DWT delays, best effort. */
#define LED_PORT           GPIOC
#define LED_PIN            GPIO_PIN_13

/* ---- Buttons: SW1 = NRST, SW2 = BOOT0 (10K pulldown R22); hardware only. */

/* ---- Battery: no MCU ADC divider; read VBAT via BQ25883 internal ADC. ---- */

/* ---- Peripheral handles (defined in main.c) ---- */
extern SPI_HandleTypeDef  hspi1;
extern I2C_HandleTypeDef  hi2c1;
extern SD_HandleTypeDef   hsd1;
extern TIM_HandleTypeDef  htim2;
extern UART_HandleTypeDef huart6;
extern ADC_HandleTypeDef  hadc1;
extern PCD_HandleTypeDef  hpcd_USB_OTG_FS;

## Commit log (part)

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2025-12-29 Create Hardware
2025-12-29 Added stuff
2025-12-29 Update README with project dependencies
    Added project dependencies to README.
2025-12-29 Update project dependencies with links in README
2025-12-29 Enhance README with images and components list
    Added images and updated components section in README.
2025-12-29 Software
2025-12-29 Fix formatting and spacing in README.md
2025-12-29 Update README with new hardware components
    Added additional hardware components to the README.
